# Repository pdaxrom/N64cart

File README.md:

# N64cart - N64 flash cartridge

* [Intro](#intro)
* [Concept](#concept)
  * [Project files](#project-files)
  * [Features](#features)
  * [Memory mapping](#memory-mapping)
* [PCB](#pcb)
  * [Order notes](#order-notes)
  * [Assembly notes](#assembly-notes)
* [Build firmware](#build-firmware)
* [Build ROM Manager](#build-rom-manager)
* [Cartridge utility](#cartridge-utility)
  * [Build](#build)
  * [How to use](#how-to-use)
  * [Remote access to the cartridge](#remote-access-to-the-cartridge)
* [ROMFS Manager](#romfs-manager)
* [Total cartridge cost (32 MB version)](#total-cartridge-cost-32-mb-version)
* [Photos of version 2](#photos-of-version-2)
* [Bill of materials for version 3](#bill-of-materials-for-version-3)
* [Photos of version 3](#photos-of-version-3)
* [Remote access from an SGI Indy](#remote-access-from-an-sgi-indy)

## Intro

N64cart is an inexpensive N64 flash cartridge you can build at home. The hardware and firmware started as a fork of Konrad Beckmann's [PicoCart64](https://github.com/kbeckmann/PicoCart64), which uses a Raspberry Pi Pico as a memory controller.

The N64 cartridge connector footprint for Eagle CAD comes from [SummerCart64](https://github.com/Polprzewodnikowy/SummerCollection).

The N64 ROM boot code is derived from [N64FlashcartMenu](https://github.com/Polprzewodnikowy/N64FlashcartMenu) and [N64 DreamOS ROM](https://github.com/khill25/Dreamdrive64/tree/main/sw/n64).

## Concept

To keep the cartridge simple and inexpensive, I used one SPI flash chip and one RP2040. Konrad's design used multiplexed PSRAM chips and two RP2040s. Flash chips rated for more than 100,000 erase/program cycles should last for many years of home use.

The RP2040's XIP interface directly addresses up to 16 MB of flash. The early design used the Extended Address (EA) register to switch between 16 MB banks on larger chips. This was slow: each bank switch required disabling XIP, switching to SPI mode to update the register, and then re-enabling XIP. N64cart now uses QSPI with 32-bit addressing, without XIP, to avoid bank switching.

The [romfs](fw/romfs) filesystem maps the sectors of stored files into a contiguous address space that the N64 accesses through the PI bus. Maximum flash capacity depends on the board version: 64 MB for version 2 with a SOIC-8 or 8 × 6 mm WSON-8 package, and 128 MB for version 3 with a SOIC-16 package.

### Project files

#### Cartridge board version 2 (SOIC-8 / WSON-8, 8 × 6 mm; 64 MB maximum)

[Schematic (PDF)](hw/n64cart-v2-soic-8.pdf)

[Schematic (Eagle CAD)](hw/n64cart-v2-soic-8.sch)

[PCB (Eagle CAD)](hw/n64cart-v2-soic-8.brd)

[Gerber files](hw/n64cart-v2-soic-8_2024-08-11.zip)

#### Cartridge board version 3 (SOIC-16; 128 MB maximum)

[Schematic (PDF)](hw/n64cart-v3-soic-16.pdf)

[Schematic (Eagle CAD)](hw/n64cart-v3-soic-16.sch)

[PCB (Eagle CAD)](hw/n64cart-v3-soic-16.brd)

[Gerber files](hw/n64cart-v3-soic-16_2024-08-11.zip)

### Features

- One LED controlled by the N64, with WS2812 RGB support on PCB version 3 (not available on PicoCart64-lite)
- A UART port accessible from the N64 (not available on PicoCart64-lite)
- USB passthrough to the N64
- Emulation of 4/16 Kbit EEPROM
- Emulation of 256 Kbit / 1 Mbit SRAM
- Emulation of 1 Mbit FlashRAM (29L1100)
- A USB utility for accessing files on the cartridge's flash chip

### Memory mapping

#### Registers

Register|Address|Mode
--------|-------|----
UART_CTRL|0x1fd01000|R-
UART_RXTX|0x1fd01004|RW
LED_CTRL|0x1fd01008|-W
SYS_CTRL|0x1fd0100c|RW
SSI_SR|0x1fd01010|RW
SSI_DR0|0x1fd01014|RW
FW_SIZE|0x1fd01018|R-

#### UART_CTRL bits

Function|Bit mask|Mode
--------|--------|----
UART_RX_AVAIL|0x01|R-
UART_TX_FREE|0x02|R-

#### UART_RXTX bits

Function|Bit mask|Mode
--------|--------|----
DATA|0xFF|RW

#### LED control bits

Function|Bit mask|Mode|Note
--------|--------|----|---
LED_ONOFF|0x01|-W|PCB v2 or PCB v3 without WS2812
LED_RGB|0x00ffffff|-W|PCB v3 only

#### SYS_CTRL bits

Function|Bit mask|Mode
--------|--------|----
EEPROM_16KBIT|0x1000|RW
FRAM_MODE|0x200|RW
SRAM_UNLOCK|0x100|RW
FLASH_MODE_QUAD|0x10|RW
FLASH_CS_HIGH|0x01|RW

#### SSI_SR bits

Function|Bit mask|Mode
--------|--------|----
SSI_SR_TFNF_BITS|0x01|R-
SSI_SR_RFNE_BITS|0x02|R-

#### SSI_DR0 bits

Function|Bit mask|Mode
--------|--------|----
DATA|0xff|RW

## PCB

### Order notes

Use a PCB thickness of 1.2 mm.

A stencil makes it easier to apply solder paste, but adds to the order cost.

### Assembly notes

After soldering the processor and flash chip, thoroughly remove flux residue from the board. Residue can cause unstable memory operation or prevent the cartridge from working.

#### PCB version 2

Populate either D2 or Q1, but not both.

Leave R1 and R6 unpopulated.

#### PCB version 3

If LED3 is populated, leave R1 and D2 unpopulated.

## Build firmware

Install the Pico SDK before building the firmware.

The default configuration is `BOARD=v3` and `REGION=ntsc`. Pass one of these options to CMake to select a different board:

- `-DBOARD=v2`: cartridge version 2 with 32/64 MB flash.
- `-DBOARD=pico`: a generic Pico cartridge with up to 16 MB of flash, without the `SI_DAT`, `SI_CLK`, `NMI`, and `INT` signals.
- `-DBOARD=pico-lite`: a PicoCart64-lite cartridge with up to 16 MB of flash, with the `SI_DAT`, `SI_CLK`, `NMI`, and `INT` signals.

Select the firmware region according to the console:

| Console | CMake option | ROM Manager video mode |
|---|---|---|
| NTSC | `-DREGION=ntsc` (default) | NTSC |
| PAL | `-DREGION=pal` | PAL |
| PAL-M / MPAL (Brazil) | `-DREGION=ntsc` (default) | MPAL |

`REGION` selects the cartridge's CIC security protocol. PAL-M consoles use the same protocol as NTSC consoles, so choose the NTSC firmware build for PAL-M too. ROM Manager gets the console's TV type from libdragon and selects the video mode automatically. No separate PAL-M build is needed, though it still needs testing on a real PAL-M console.

From the repository root, build the default configuration:

```sh
cd fw
mkdir -p build
cd build
cmake ..
make -j
```

For example, use `cmake .. -DBOARD=v2 -DREGION=pal` to build for a version 2 cartridge and a PAL console.

Hold the cartridge's bootloader button while connecting it via USB, then copy `fw/build/n64cart.uf2` to the `RPI-RP2` drive.

## Build ROM Manager

Install an N64 toolchain with [libdragon](https://github.com/DragonMinded/libdragon) built from the `opengl` branch.

Pass `BOARD=pico` to `make` for a generic Pico cartridge, or `BOARD=pico-lite` for a PicoCart64-lite cartridge. Both configurations support flash chips of up to 16 MB. No `REGION` option is needed: video mode selection is automatic for NTSC, PAL, and PAL-M consoles.

From the repository root:

```sh
cd rom
make
```

## Cartridge utility

The utility formats cartridge memory and reads and writes files. Use it to upload ROMs or change the background image.

### Build

For Linux and macOS, install the libusb development files. From the repository root:

```sh
cd utils
make
```

To build for Windows, install the MinGW toolchain. From the repository root:

```sh
cd utils
make SYSTEM=Windows
```

### How to use

Run the following commands from the `utils` directory. Before using a new cartridge, format it and upload ROM Manager:

```sh
./usb-romfs format
./usb-romfs push ../rom/n64cart-manager.z64
```

Upload a ROM, for example:

```sh
./usb-romfs push game.z64
```

To change the background image:

```sh
./usb-romfs push picture.jpg background.jpg
```

Available commands (angle brackets indicate placeholders; square brackets indicate optional arguments):

```text
./usb-romfs help
./usb-romfs bootloader
./usb-romfs reboot
./usb-romfs format
./usb-romfs list [-h] [path]
./usb-romfs delete <remote path>
./usb-romfs mkdir <remote path>
./usb-romfs rmdir <remote path>
./usb-romfs rename <source> <destination> [--create-dirs]
./usb-romfs push [--fix-rom] [--fix-pi-bus-speed[=12..FF]] <local filename> [<remote path>]
./usb-romfs pull <remote path> [<local filename>]
./usb-romfs free
```

### Remote access to the cartridge

If your computer cannot connect to the cartridge directly, you can access it through a USB-connected proxy computer. This is useful for older systems without USB, such as an SGI Indy. Build the remote-access utilities from the `utils` directory:

```sh
make remote
```

If the client and proxy use different architectures or operating systems, cross-compile `remote-romfs` for the client by specifying the compiler:

```sh
make CC="mips-sgi-irix6o32-gcc" remote-romfs
```

Copy `remote-romfs` to the client. On the proxy computer, connect the cartridge via USB and start the proxy:

```sh
./proxy-romfs
```

On the client, `remote-romfs` takes the same commands as `usb-romfs`. Add the proxy's IP address before the command:

```text
./remote-romfs <proxy IP address> <command ...>
```

[Photos of remote access from an SGI Indy](#remote-access-from-an-sgi-indy)

## ROMFS Manager

[ROMFS Manager](utils/romfs-gui) is a desktop application built with Qt. You can use it to browse, upload, and download files on N64cart over USB or through a remote proxy.

## Total cartridge cost (32 MB version)

The following is an example cost breakdown for the 32 MB version. Shipping can
cost more than the components when ordering only one or two of each item.
Larger orders may qualify for free shipping.

Seller|Delivery cost|Components
------|-------------|---
[Chicago Electronic Distributors](https://chicagodist.com/)|$6-$11|RP2040
[Arrow](https://www.arrow.com/)|Free for orders > $50|SPI flash, resistors, capacitors, etc.
[JLCPCB](https://jlcpcb.com/)|$22.40|PCB

In this example, five PCBs cost $2 for the first PCB design in an order, or $4 for each additional design.

The most expensive components:

Component|Quantity|Price
---------|---|-----
RP2040|1|$1
W25Q256JVEIQ|1|$4.24
ABLS-12.000MHZ-B4-T|1|$0.26
UJ2-MIBH-G-SMT-TR|1|$0.45
LDI1117-3.3U|1|$0.34
BAT60AE6327HTSA1|2|$0.93

The remaining components (LEDs, resistors, and capacitors) came from existing stock and cost less than $1 in total.

The estimated total cost of the PCB and components is approximately $9, excluding shipping.

## Photos of version 2

## Bill of materials for version 3

Part|Value|Device|Package
----|-----|------|-------
C1|100n|C-EUC0402|C0402
C2|100n|C-EUC0402|C0402
C3|100n|C-EUC0402|C0402
C4|100n|C-EUC0603|C0603
C5|100n|C-EUC0402|C0402
C6|100n|C-EUC0402|C0402
C7|100n|C-EUC0603|C0603
C8|100n|C-EUC0402|C0402
C9|100n|C-EUC0402|C0402
C10|1uF|C-EUC0402|C0402
C11|100n|C-EUC0402|C0402
C12|100n|C-EUC0402|C0402
C13|1uF|C-EUC0402|C0402
C14|100n|C-EUC0402|C0402
C15|27pF|C-EUC0402|C0402
C16|27pF|C-EUC0402|C0402
C22|10u|C-EUC0805|C0805
D1|SL02-GS08|SL02-GS08|SOD-123
D2|GREEN|LED0603|0603
D3|RED|LED0603|0603
IC1|RP2040-QFN56|RP2040-QFN56|QFN-56
LED3|XL-5050RGBC-WS2812B|XL-5050RGBC-WS2812B|XL5050RGBCWS2812B
Q1|BSS84|BSS84|SOT23
R1|1K|R-EU_R0603|R0603
R2|1K|R-EU_R0402|R0402
R3|1K|R-EU_R0402|R0402
R4|27|R-EU_R0402|R0402
R5|27|R-EU_R0402|R0402
R12|1K|R-EU_R0603|R0603
S1||10-XX|B3F-10XX
U$1|LDI1117-3.3U|LDI1117-3.3U|LDI1117-3.3U
U2||USB|USB-MICRO-SMD
U4|MX66L1G45GMI-08G|MX66L1G45GMI-08G|SOP_16
XTAL1|ABLS-12.000MHZ-B4-T|ABLS-12.000MHZ-B4-T|XTAL_ABLS_ABR

## Photos of version 3

## Remote access from an SGI Indy

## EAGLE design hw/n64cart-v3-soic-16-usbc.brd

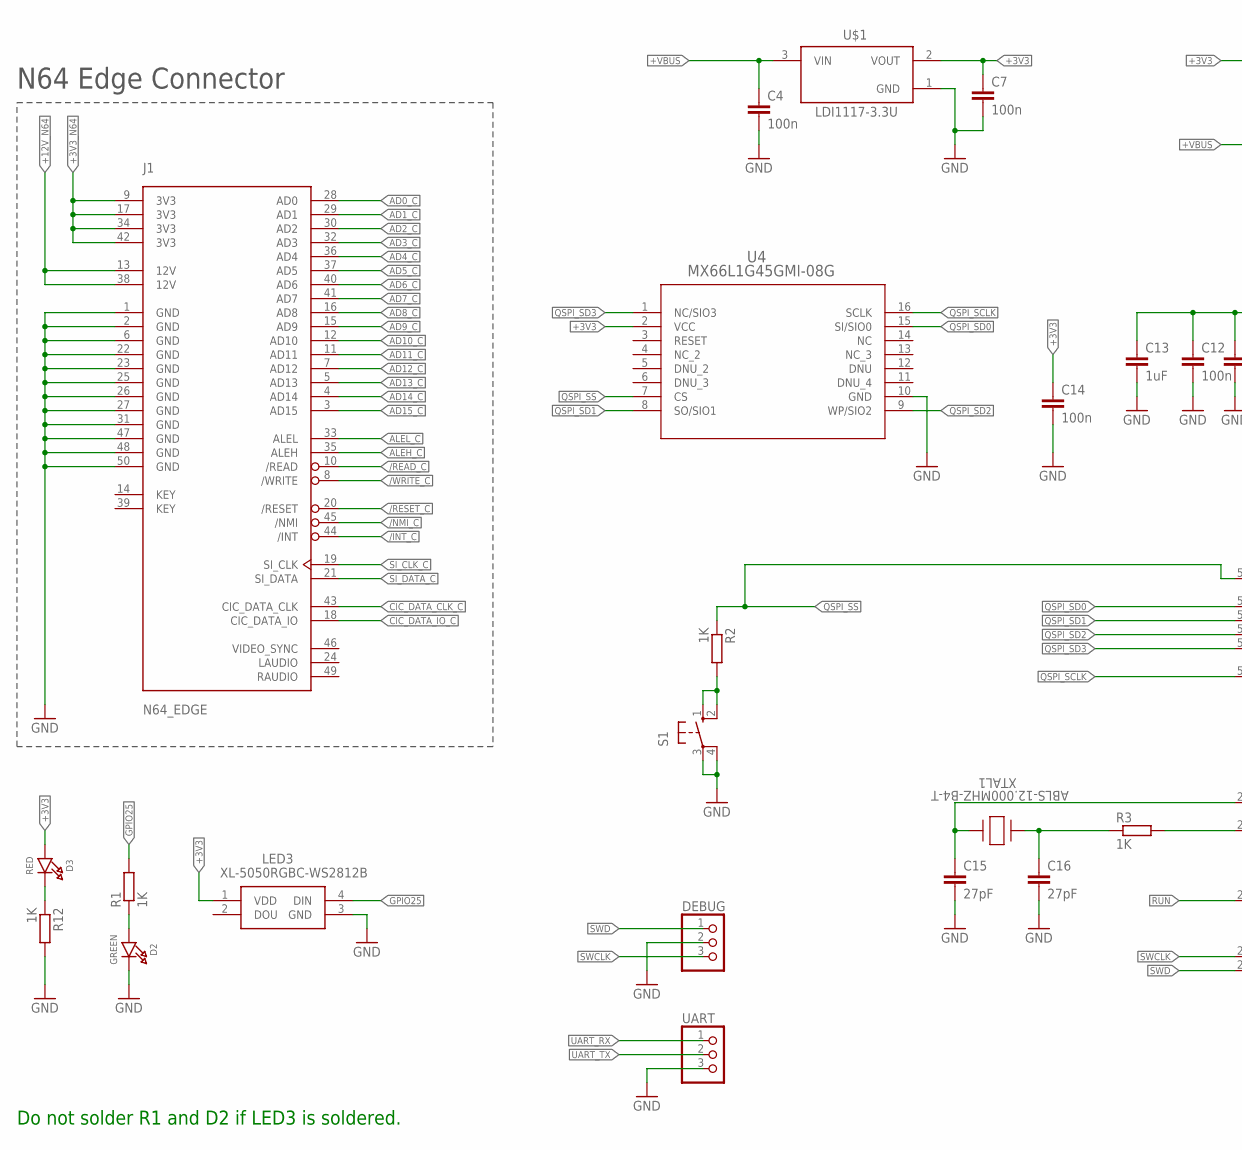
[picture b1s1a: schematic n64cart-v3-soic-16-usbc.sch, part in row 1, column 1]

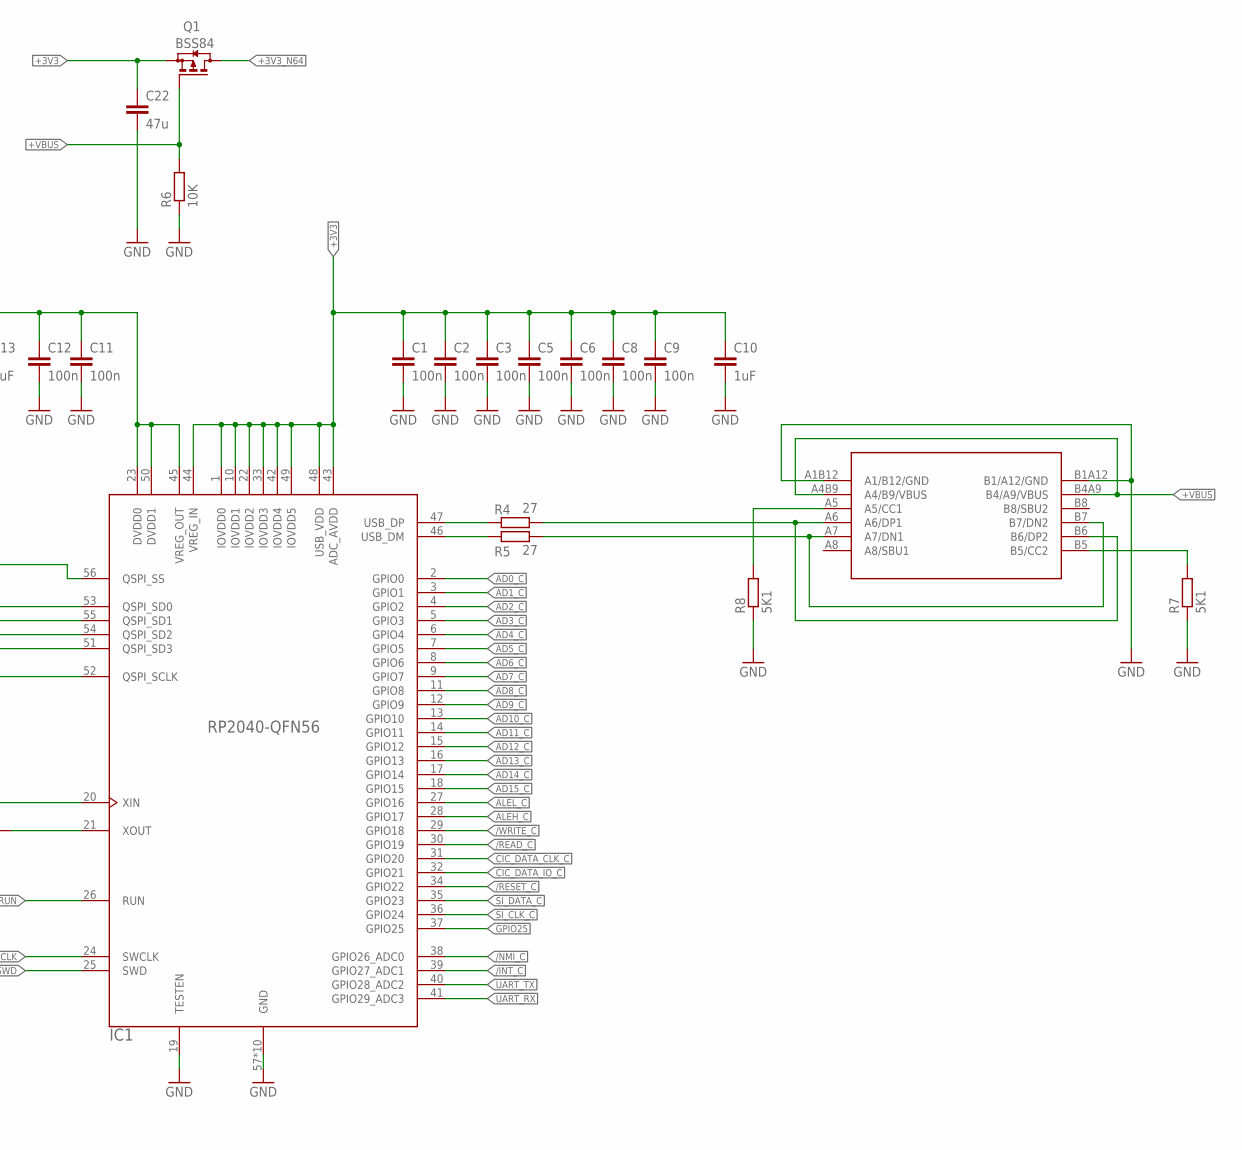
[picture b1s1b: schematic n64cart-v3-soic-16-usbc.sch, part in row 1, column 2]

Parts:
C1, C2, C3, C5, C6, C8, C9, C11, C12, C14: 100n; C0402
C4, C7: 100n; C0603
C10, C13: 1uF; C0402
C15, C16: 27pF; C0402
C22: 47u; C0805
D2: GREEN; CHIPLED_0603_NOOUTLINE
D3: RED; CHIPLED_0603_NOOUTLINE
DEBUG: PINHD-1X3; 1X03
IC1: RP2040-QFN56; RP2040-QFN-56
J1: N64_EDGE
J2: GT-USB-7010
LED3: XL-5050RGBC-WS2812B; XL5050RGBCWS2812B
Q1: BSS84; SOT23
R1, R12: 1K; R0603
R2, R3: 1K; R0402
R4, R5: 27; R0402
R6: 10K; R0603
R7, R8: 5K1; R0603
S1: 10-XX; B3F-10XX
U4: MX66L1G45GMI-08G; SOP_16L_300_MAC-L
U$1: LDI1117-3.3U
UART: PINHD-1X3; 1X03
XTAL1: ABLS-12.000MHZ-B4-T; XTAL_ABLS_ABR

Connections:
+3V3: C1.1, C2.1, C3.1, C5.1, C6.1, C7.1, C8.1, C9.1, C10.1, C14.1, C22.1, D3.A, IC1.1 (IOVDD0), IC1.10 (IOVDD1), IC1.22 (IOVDD2), IC1.33 (IOVDD3), IC1.42 (IOVDD4), IC1.43 (ADC_AVDD), IC1.44 (VREG_IN), IC1.48 (USB_VDD), IC1.49 (IOVDD5), LED3.1 (VDD), Q1.2 (S), U4.2 (VCC), U$1.2 (VOUT)
+3V3_N64: J1.9 (3V3), J1.17 (3V3), J1.34 (3V3), J1.42 (3V3), Q1.3 (D)
+12V_N64: J1.13 (12V), J1.38 (12V)
+VBUS: C4.1, J2.A4B9 (A4/B9/VBUS), J2.B4A9 (B4/A9/VBUS), Q1.1 (G), R6.2, U$1.3 (VIN)
/INT_C: IC1.39 (GPIO27_ADC1), J1.44 (/INT)
/NMI_C: IC1.38 (GPIO26_ADC0), J1.45 (/NMI)
/READ_C: IC1.30 (GPIO19), J1.10 (/READ)
/RESET_C: IC1.34 (GPIO22), J1.20 (/RESET)
/WRITE_C: IC1.29 (GPIO18), J1.8 (/WRITE)
AD0_C: IC1.2 (GPIO0), J1.28 (AD0)
AD1_C: IC1.3 (GPIO1), J1.29 (AD1)
AD2_C: IC1.4 (GPIO2), J1.30 (AD2)
AD3_C: IC1.5 (GPIO3), J1.32 (AD3)
AD4_C: IC1.6 (GPIO4), J1.36 (AD4)
AD5_C: IC1.7 (GPIO5), J1.37 (AD5)
AD6_C: IC1.8 (GPIO6), J1.40 (AD6)
AD7_C: IC1.9 (GPIO7), J1.41 (AD7)
AD8_C: IC1.11 (GPIO8), J1.16 (AD8)
AD9_C: IC1.12 (GPIO9), J1.15 (AD9)
AD10_C: IC1.13 (GPIO10), J1.12 (AD10)
AD11_C: IC1.14 (GPIO11), J1.11 (AD11)
AD12_C: IC1.15 (GPIO12), J1.7 (AD12)
AD13_C: IC1.16 (GPIO13), J1.5 (AD13)
AD14_C: IC1.17 (GPIO14), J1.4 (AD14)
AD15_C: IC1.18 (GPIO15), J1.3 (AD15)
ALEH_C: IC1.28 (GPIO17), J1.35 (ALEH)
ALEL_C: IC1.27 (GPIO16), J1.33 (ALEL)
CIC_DATA_CLK_C: IC1.31 (GPIO20), J1.43 (CIC_DATA_CLK)
CIC_DATA_IO_C: IC1.32 (GPIO21), J1.18 (CIC_DATA_IO)
GND: C1.2, C2.2, C3.2, C4.2, C5.2, C6.2, C7.2, C8.2, C9.2, C10.2, C11.2, C12.2, C13.2, C14.2, C15.2, C16.2, C22.2, D2.C, DEBUG.2, IC1.19 (TESTEN), IC1.57 (GND), IC1.58 (GND), IC1.59 (GND), IC1.60 (GND), IC1.61 (GND), IC1.62 (GND), IC1.63 (GND), IC1.64 (GND), IC1.65 (GND), IC1.66 (GND), J1.1 (GND), J1.2 (GND), J1.6 (GND), J1.22 (GND), J1.23 (GND), J1.25 (GND), J1.26 (GND), J1.27 (GND), J1.31 (GND), J1.47 (GND), J1.48 (GND), J1.50 (GND), J2.A1B12 (A1/B12/GND), J2.B1A12 (B1/A12/GND), LED3.3 (GND), R6.1, R7.1, R8.1, R12.2, S1.3, S1.4 (P1), U4.10 (GND), U$1.1 (GND), UART.3
GPIO25: IC1.37 (GPIO25), LED3.4 (DIN), R1.2
unnamed: J2.B5 (B5/CC2), R7.2
unnamed: J2.A5 (A5/CC1), R8.2
unnamed: D3.C, R12.1
unnamed: C11.1, C12.1, C13.1, IC1.23 (DVDD0), IC1.45 (VREG_OUT), IC1.50 (DVDD1)
unnamed: J2.A7 (A7/DN1), J2.B7 (B7/DN2), R5.2
unnamed: J2.A6 (A6/DP1), J2.B6 (B6/DP2), R4.2
unnamed: D2.A, R1.1
unnamed: R2.2, S1.1 (S), S1.2 (S1)
unnamed: C16.1, R3.1, XTAL1.1
unnamed: C15.1, IC1.20 (XIN), XTAL1.2
unnamed: IC1.21 (XOUT), R3.2
unnamed: IC1.47 (USB_DP), R4.1
unnamed: IC1.46 (USB_DM), R5.1
QSPI_SCLK: IC1.52 (QSPI_SCLK), U4.16 (SCLK)
QSPI_SD0: IC1.53 (QSPI_SD0), U4.15 (SI/SIO0)
QSPI_SD1: IC1.55 (QSPI_SD1), U4.8 (SO/SIO1)
QSPI_SD2: IC1.54 (QSPI_SD2), U4.9 (WP/SIO2)
QSPI_SD3: IC1.51 (QSPI_SD3), U4.1 (NC/SIO3)
QSPI_SS: IC1.56 (QSPI_SS), R2.1, U4.7 (CS)
RUN: IC1.26 (RUN)
SI_CLK_C: IC1.36 (GPIO24), J1.19 (SI_CLK)
SI_DATA_C: IC1.35 (GPIO23), J1.21 (SI_DATA)
SWCLK: DEBUG.3, IC1.24 (SWCLK)
SWD: DEBUG.1, IC1.25 (SWD)
UART_RX: IC1.41 (GPIO29_ADC3), UART.1
UART_TX: IC1.40 (GPIO28_ADC2), UART.2

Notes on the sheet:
N64 Edge Connector
Do not solder R1 and D2 if LED3 is soldered.

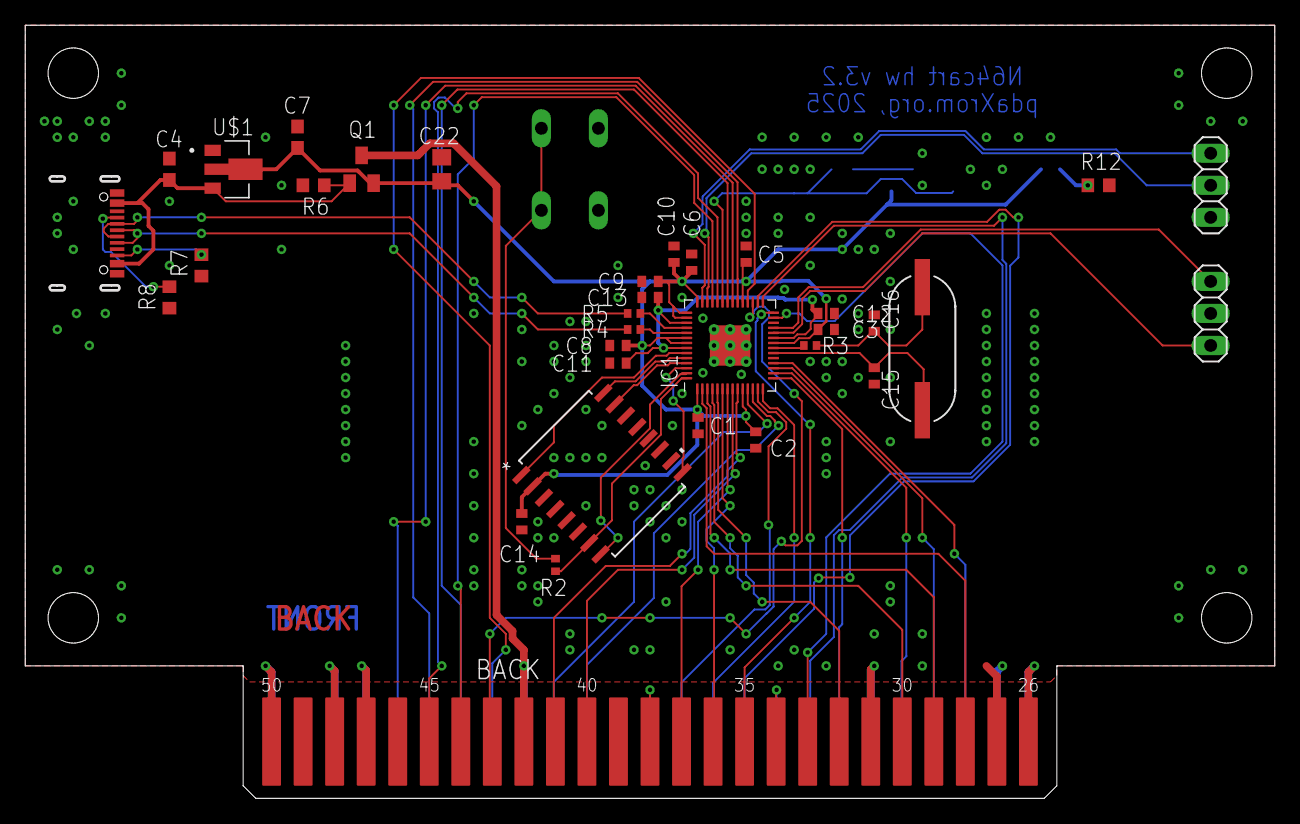
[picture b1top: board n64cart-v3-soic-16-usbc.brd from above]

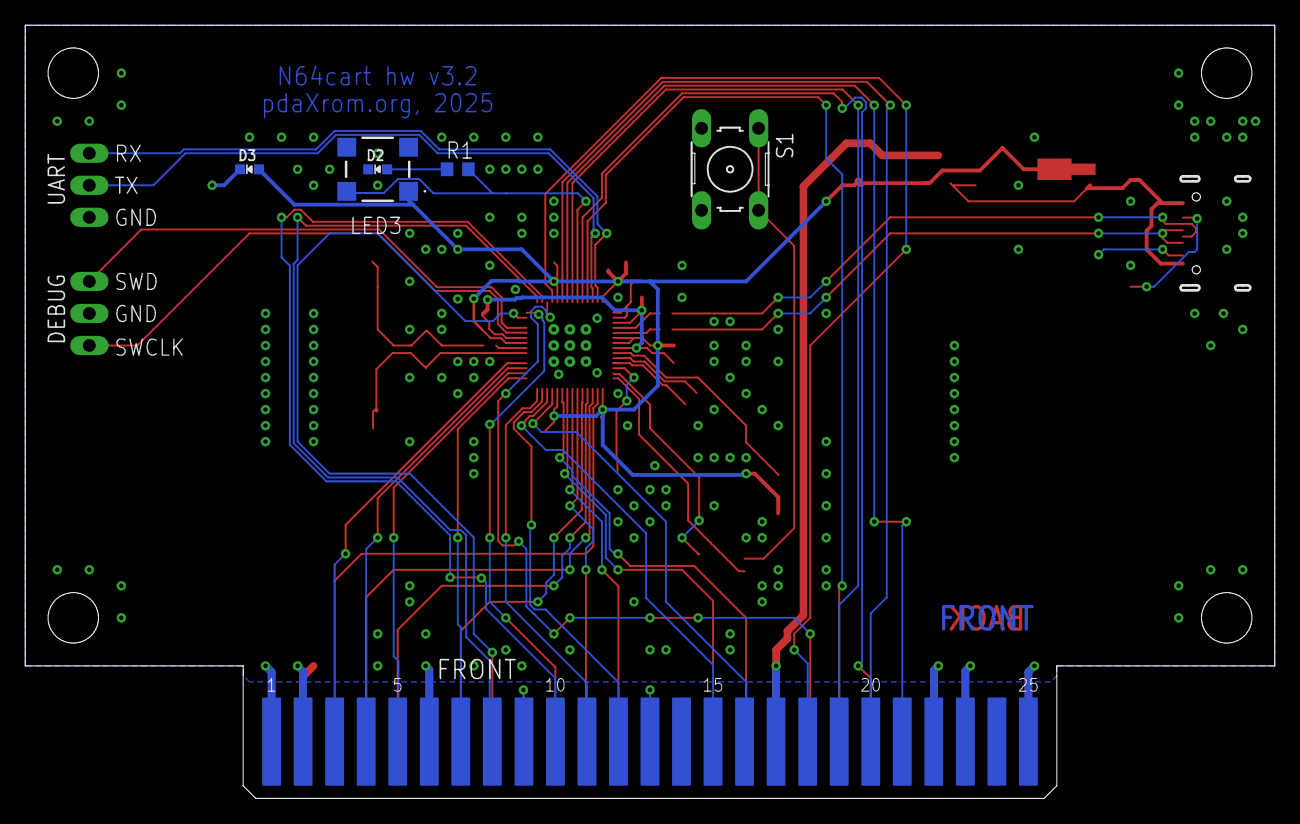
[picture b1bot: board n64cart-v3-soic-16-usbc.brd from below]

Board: 2 copper layers, 99.1 x 61.3 mm, 39 parts (5 on the bottom side), 56 nets.

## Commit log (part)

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2022-08-02 initial
2022-08-02 fixed wrong NMI and INT for cartridge schematic
2022-08-05 cartridge schematic
2022-08-05 fixed for current hw
2022-08-06 write to card support initial
2022-08-06 UART
2022-08-07 led port
2022-08-07 show NMI status
2022-08-07 some optmization for PI
2022-08-08 usb rom uploader
2022-08-08 firmware source moved to fw directory
2022-08-08 bootload rom pages info
2022-08-08 fixed error messages
2022-08-08 rom page control port
2022-08-08 switch flash rom to lower and upper page
2022-08-09 usb transfer with 4096KB packets
2022-08-10 usb packet reduced to 32 bytes
2022-08-10 pi logic moved to core1
2022-08-10 pi sram initial
2022-08-10 fixed wrong byte order in sram
2022-08-11 support for N64 and V64 roms
2022-08-11 support for user background pictures
2022-08-13 added capacitor to VBUS
2022-08-14 test rom sources
2022-09-10 fixed build test rom
2022-09-10 usage info
2022-09-10 latest version
2022-09-10 cartrigde case
2022-09-10 fix photos order
2022-09-10 Ordering info screen
2022-09-10 Ordering info image
2022-09-10 memmap info
2022-09-10 fix table
2022-09-11 64MB flash support
2022-09-11 schematic in pdf
2022-10-04 fixed for build on macos
2022-10-04 added VID PID, thanks to https://pid.codes
2022-10-05 fixed usb info, added windows build for usb utility
2022-10-06 detect rom chip and configure system and pi bus frequencies
2022-10-13 fixed macos usb enumeration error
2022-10-13 removed unnecessary comments, fixed headers
2023-02-10 implemented delete command
2023-02-22 write file initial
2023-02-22 fixed find list entry, renamed get error string function
2023-02-22 read file initial
2023-04-23 compilation warnings fix, fixed close function for read
2023-04-23 read file fixed
2023-06-25 PI interrupts
2023-06-26 romfs mapper initial
2023-06-26 cleanup sources
2023-10-21 added missed header file
2023-10-23 read flash in spi 4byte fast read mode
2023-10-24 use spi quad read (24bit address yet)
2023-10-24 flash fast quad read with EC (in SPI mode)
2023-10-24 romfs crossplatform fixes
2023-10-25 initial spi/quad mode switcher, new usb utility for romfs
2023-10-25 fixed switching between spi and quad modes
2023-10-25 removed unnecessary comments and code
2023-10-25 cleanup
2023-10-25 removed duplicate swap for 16 bit bus data
2023-10-25 removed old usb uploader, added docs for rp2040 and flash chip
2023-10-25 optimization for read block data from flash
2023-11-01 usb romfs code optimization, reboot in bootloader option
2023-11-01 added help, parameters checking and help for usb-romfs utility
2023-11-16 spi access to flash from N64
2023-11-17 remove object directory on make clean
2023-11-17 disabled debug info output
2023-11-17 fixed byte order in file attributes
2023-11-17 usb reboot command, removed sram flash area - need to load it from romfs
2023-11-19 RAM optimization
2023-11-19 fmall fixes
2023-11-24 select rom menu
2023-11-24 show progress
2023-11-25 ROM launcher based on boot code from SummerCart64
2023-11-26 test rom updated for build with libdragon dev branch
2023-11-30 fix menu overflow
2023-11-30 stb_image to read pictures
2023-12-01 resize user background picture
2023-12-01 test-rom renamed to n64cart-manager
2023-12-04 16x16 font for hi-res mode
2023-12-11 pi bus speed fix moved to usb file uploader
2023-12-12 return error status
2023-12-13 flash read optimization
2023-12-13 use quad continuous read mode
2023-12-15 cic io implemented with gpio interrupts
2023-12-15 reset cic io on cic init
2023-12-31 SI initial implementation
2024-01-20 si irq output without calculations
2024-02-20 fixed eeprom bits buffer size
2024-02-20 move eeprom to n64 accessible pi sram
2024-02-20 some optimization for SI code
2024-02-20 preventing writing to SI with an incorrect command
2024-02-21 set double value for PI bus freq
2024-02-21 optimization for PI bus control
2024-02-22 overclocking to use default pi bus freq settings (0x1240)
2024-02-24 update n64 rom manager
2024-02-24 testing dreamdrive64 rom loader
2024-02-24 set freq to 342MHz
2024-02-25 limit filename length in menu
2024-02-25 image updated
2024-02-25 fixed array size, to prevent out of bounds when store the name and parameters of a save game file
2024-02-29 use deleted entries if no empty available
2024-03-12 rp2040 usb mapped into n64 pi space initial usb device driver for N64, ported from rp2040 fixed occasional spi flash reading errors (stuck bit) in high addresses
2024-07-10 fix updated for new libdragon
2024-07-15 cartridge flash 128MB
2024-07-15 1Gbit flash schmatic and board
2024-07-30 moved to 128MB_cartridge branch
2024-08-02 initial software support
2024-08-05 romfs updated for 128MB flash
2024-08-05 firmware 128MB support
2024-08-06 onboard rgb led support
2024-08-06 removed page from flash chip info
2024-08-06 usbd initialization
2024-08-06 configuration for v1/v2 boards
2024-08-06 moved to board configuration
2024-08-06 datasheets
2024-08-06 disabled xosc startup delay
2024-08-06 fix alloca header
2024-08-11 configure ntsc/pal region
2024-08-11 1Gbit pdf schematic
2024-08-11 Update readme and photos for cartridge version 3
2024-08-11 schematics renamed by version and flash chip package
2024-08-12 align flash list and map to flash sector size
2024-08-12 flash chip 24bit addressing support
2024-08-13 fixed compatibility with single chip picocard (flash chip 16MB or less)
2024-08-13 PAL firmware how to
2024-08-15 updated for pico sdk v2.0
2024-08-15 compatibility with pico sdk 1.5
2024-08-16 fixed schematic pdf v2
2024-08-17 Firmware updated for PicoCart64-lite
2024-08-17 use led configuration from board config file
2024-08-17 uart disabled for pico-lite
2024-08-17 byteswap for save files
2024-08-18 swap bytes for sram saves
2024-08-27 optimize io to cartridge peripheral registers
2024-10-04 romfs cosmetic changes
2024-10-27 cmake project for rom
2024-10-27 moved uart log messages to syslog, boot screen statuses
2024-10-27 rom source structure updated
2024-10-27 clean cmake rules
2024-11-02 moved usb initialization before video initialization, show system initialization steps
2024-11-03 missed source
2024-11-03 check for sed utility
2024-11-03 fix getting host system name
2024-11-03 fix linker
2024-11-03 disable verbose build by defailt
2024-11-03 version update
2024-11-03 WCID compatible USB device
2024-11-03 usb version remark
2024-11-03 build script
2024-11-04 read map table from file start sector
2024-11-04 Check file extension, image loading and viewer moved to separate sources
2024-11-05 fixed image viewer crash on big images
2024-11-05 missed pull down resistor for V3
2024-11-05 V3 updated
2024-11-05 missed pulldown resistor for V2
2024-11-09 write save file if updated
2024-11-09 scrolling text for long file names
2024-11-09 autorepeat for pressed file selection keys
2024-11-13 fix warnings
2024-11-13 removed unused files
2024-11-13 NES, SNES emulation support
2024-11-13 fix don't save empty save file
2025-01-04 gc/gbc/sms emulators support
2025-01-09 updated patch for latest libdragon
2025-01-09 moved to libdragon header
2025-01-21 usb type-c board with soic-16
2025-03-15 flash ram emulation initial
2025-03-15 fix flash ram vendor id
2025-03-16 init empty eeprom/flash with 0xff
2025-03-16 show message when reading save file
2025-06-05 proxy server initial
2025-06-05 removed unused code
2025-06-05 format fixed
2025-06-05 remote connect to usb romfs
2025-06-05 network support library
2025-06-05 irix build fix
2025-06-08 fix rom type detection
2025-06-08 check for proxy ip parameter
2025-06-08 fix error messages
2025-06-08 romfs proxy and remote client
2025-06-22 updated simple connection lib
2025-07-05 use static sector buffer
2025-07-05 linux compilation fix
2025-07-05 fix windows compilation
2025-07-05 irix gcc compilation fix
2025-07-05 win32 prebuild utils
2025-07-05 remote connection images
2025-08-03 option to disable file deletion
2025-09-14 The following changes have been added to romfs: - show romfs free space - automatic tests for file system - prevent to use wrong read/write operation for opened/created file - reclaim list entry and 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
2025-11-16 add support for pseudo-directories to romfs
2025-12-27 add romfs manager qt gui
2025-12-27 add romfs manager screenshot
2025-12-27 fix screenshot
2026-01-21 fix remove PI_STATUSes added to libdragon
2026-01-21 fix make build
2026-03-26 Add auto boot support
2026-03-29 fix sources format
2026-04-05 fix wrong mapping in flash ram emulation
2026-04-07 fix romfs-gui transport and file transfer error handling
2026-04-07 add show git build hash in about dialog
2026-04-11 add missing ignores
2026-04-11 starting to add boot settings support
2026-04-11 auto boot now working with setting
2026-04-11 fixed auto boot. consumer settings wip
2026-04-11 just make consumer mode a hard coded option atm
2026-04-11 auto boot just detects filename. force consumer mode by default
2026-06-06 use vcpkg libusb and add linux deploy bundle
2026-06-06 fix windows libusb runtime deployment
2026-06-06 avoid pkg-config dependency on windows
2026-06-06 auto-install romfs-gui vcpkg dependencies
2026-06-06 update romfs-gui localization and libusb lookup
2026-06-06 fix romfs-gui about localization on macos
2026-06-06 add romfs-gui pt-br de and es translations
2026-06-07 sort romfs-gui language list alphabetically
2026-06-07 implement romfs write semantics
2026-06-07 fix romfs-gui homebrew tool lookup
2026-06-13 fix USB ROMFS refresh display handling
2026-06-13 fix delay USB flash access until splash is visible
2026-06-13 fix keep USB splash active while commands are flowing

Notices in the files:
parts and their libraries:
COPYRIGHT: Copyright (C) 2022 Ultra Librarian. All rights reserved.
COPYRIGHT: Copyright (C) 2024 Ultra Librarian. All rights reserved.
